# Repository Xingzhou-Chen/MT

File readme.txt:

The codes are under the path: ~/bppy/main/final/
Codes of step-wise differential sensor is in ~/bppy/main/step/
The path to the results: ~/bppy/Thesis_Results/

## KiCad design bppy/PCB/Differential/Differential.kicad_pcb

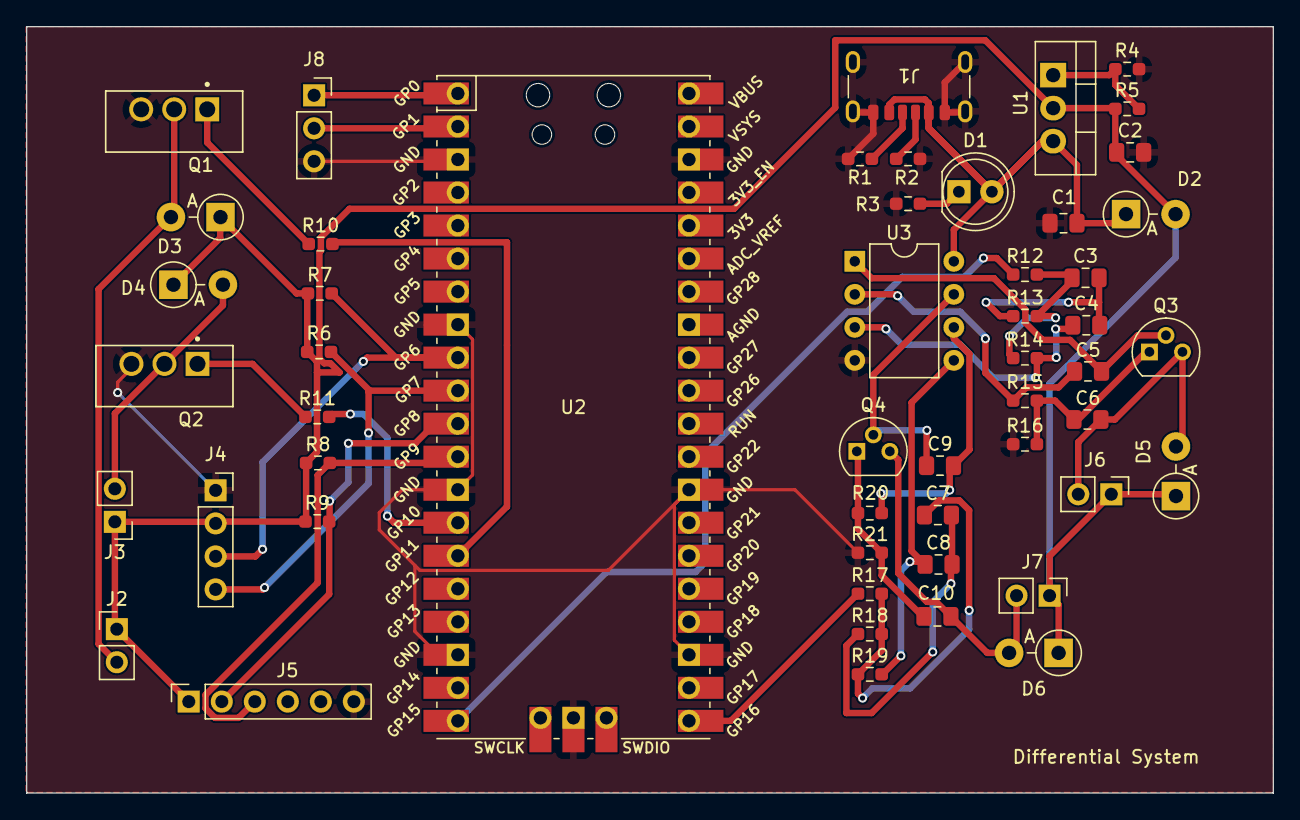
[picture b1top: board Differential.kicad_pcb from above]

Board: 2 copper layers, 95.9 x 58.9 mm, 52 parts (0 on the bottom side), 35 nets.

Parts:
C1, C6, C10: 0.1u; C_0805_2012Metric_Pad1.18x1.45mm_HandSolder
C2, C3, C7: 1u; C_0805_2012Metric_Pad1.18x1.45mm_HandSolder
C4, C5, C8, C9: 100n; C_0805_2012Metric_Pad1.18x1.45mm_HandSolder
D1: LED; LED_D5.0mm
D2, D3, D4, D5, D6: 1N4002; D_DO-41_SOD81_P3.81mm_Vertical_AnodeUp
J1: USB_C_Receptacle_PowerOnly_6P; USB_C_Receptacle_GCT_USB4125-xx-x-0190_6P_TopMnt_Horizontal
J2: Middle_Valve; PinHeader_1x02_P2.54mm_Vertical
J3: Pump; PinHeader_1x02_P2.54mm_Vertical
J4: Sensor_AMS; PinSocket_1x04_P2.54mm_Vertical
J5: Sensor_HX; PinSocket_1x06_P2.54mm_Vertical
J6: Valve_Cuff; PinHeader_1x02_P2.54mm_Vertical
J7: Valve_Baseline; PinHeader_1x02_P2.54mm_Vertical
J8: UART; PinSocket_1x03_P2.54mm_Vertical
Q1, Q2: IRLIZ44N; TO254P1054X469X1930-3
Q3, Q4: 2N2222A; TO-92
R1, R2: 5.1k; R_0603_1608Metric_Pad0.98x0.95mm_HandSolder
R3: 2.52k; R_0603_1608Metric_Pad0.98x0.95mm_HandSolder
R4: 390; R_0603_1608Metric_Pad0.98x0.95mm_HandSolder
R5: 240; R_0603_1608Metric_Pad0.98x0.95mm_HandSolder
R6, R7, R8, R9: 4.7k; R_0603_1608Metric_Pad0.98x0.95mm_HandSolder
R10, R11: 1k; R_0603_1608Metric_Pad0.98x0.95mm_HandSolder
R12, R14, R15, R17, R19, R20: 100k; R_0603_1608Metric_Pad0.98x0.95mm_HandSolder
R13, R18: 33k; R_0603_1608Metric_Pad0.98x0.95mm_HandSolder
R16, R21: 10; R_0603_1608Metric_Pad0.98x0.95mm_HandSolder
U1: LM317; TO-220-3_Vertical
U2: Pico; RPi_Pico_SMD_TH
U3: NJM2114; DIP-8_W7.62mm

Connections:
+3.3V: C2.1, D2.2 (A), D3.1 (K), D4.1 (K), D5.1 (K), D6.1 (K), J2.1, J3.1, J4.2, J5.1, J6.1, J7.1, R5.1, R6.1, R7.1, R8.1, R9.1, U1.2 (VO)
+5V: C1.1, D1.2 (A), D2.1 (K), J1.A9 (VBUS), J1.B9 (VBUS), U1.3 (VI), U3.8 (V+)
/Middle_Valve: R10.2, U2.15 (GPIO11)
/Pump: R11.2, U2.14 (GPIO10)
/RX: J8.2, U2.2 (GPIO1)
/SCL0: J5.3, R8.2, U2.12 (GPIO9)
/SCL1: J4.4, R6.2, U2.10 (GPIO7)
/SDA0: J5.2, R9.2, U2.11 (GPIO8)
/SDA1: J4.3, R7.2, U2.9 (GPIO6)
/TX: J8.1, U2.1 (GPIO0)
Baseline_Valve: R17.1, U2.21 (GPIO16)
Cuff_Valve: R12.1, U2.20 (GPIO15)
GND: C1.2, C2.2, J1.A12 (GND), J1.B12 (GND), J1.S1 (SHIELD), J4.1, J5.6, J8.3, Q1.3 (S), Q2.3 (S), R1.2, R2.2, R3.1, R4.2, R16.1, R21.1, U2.3 (GND), U2.8 (GND), U2.13 (GND), U2.18 (GND), U2.23 (GND), U2.28 (GND), U2.38 (GND), U2.42 (GND), U3.4 (V-)
unnamed: C3.1, R12.2, R13.2, R14.1
unnamed: C3.2, C4.2, R13.1
unnamed: C7.1, R17.2, R18.2, R19.1
unnamed: C7.2, C8.2, R18.1
unnamed: D1.1 (K), R3.2
unnamed: D3.2 (A), J2.2, Q1.2 (D)
unnamed: D4.2 (A), J3.2, Q2.2 (D)
unnamed: C6.1, D5.2 (A), J6.2, Q3.3 (C)
unnamed: C10.1, D6.2 (A), J7.2, Q4.3 (C)
unnamed: J1.A5 (CC1), R2.1
unnamed: J1.B5 (CC2), R1.1
unnamed: Q1.1 (G), R10.1
unnamed: Q2.1 (G), R11.1
unnamed: C5.1, Q3.2 (B), U3.1
unnamed: C6.2, Q3.1 (E), R15.2, R16.2
unnamed: C9.1, Q4.2 (B), U3.7
unnamed: C10.2, Q4.1 (E), R20.2, R21.2
unnamed: R4.1, R5.2, U1.1 (ADJ)
unnamed: C4.1, R14.2, U3.3 (+)
unnamed: C5.2, R15.1, U3.2 (-)
unnamed: C8.1, R19.2, U3.5 (+)
unnamed: C9.2, R20.1, U3.6 (-)

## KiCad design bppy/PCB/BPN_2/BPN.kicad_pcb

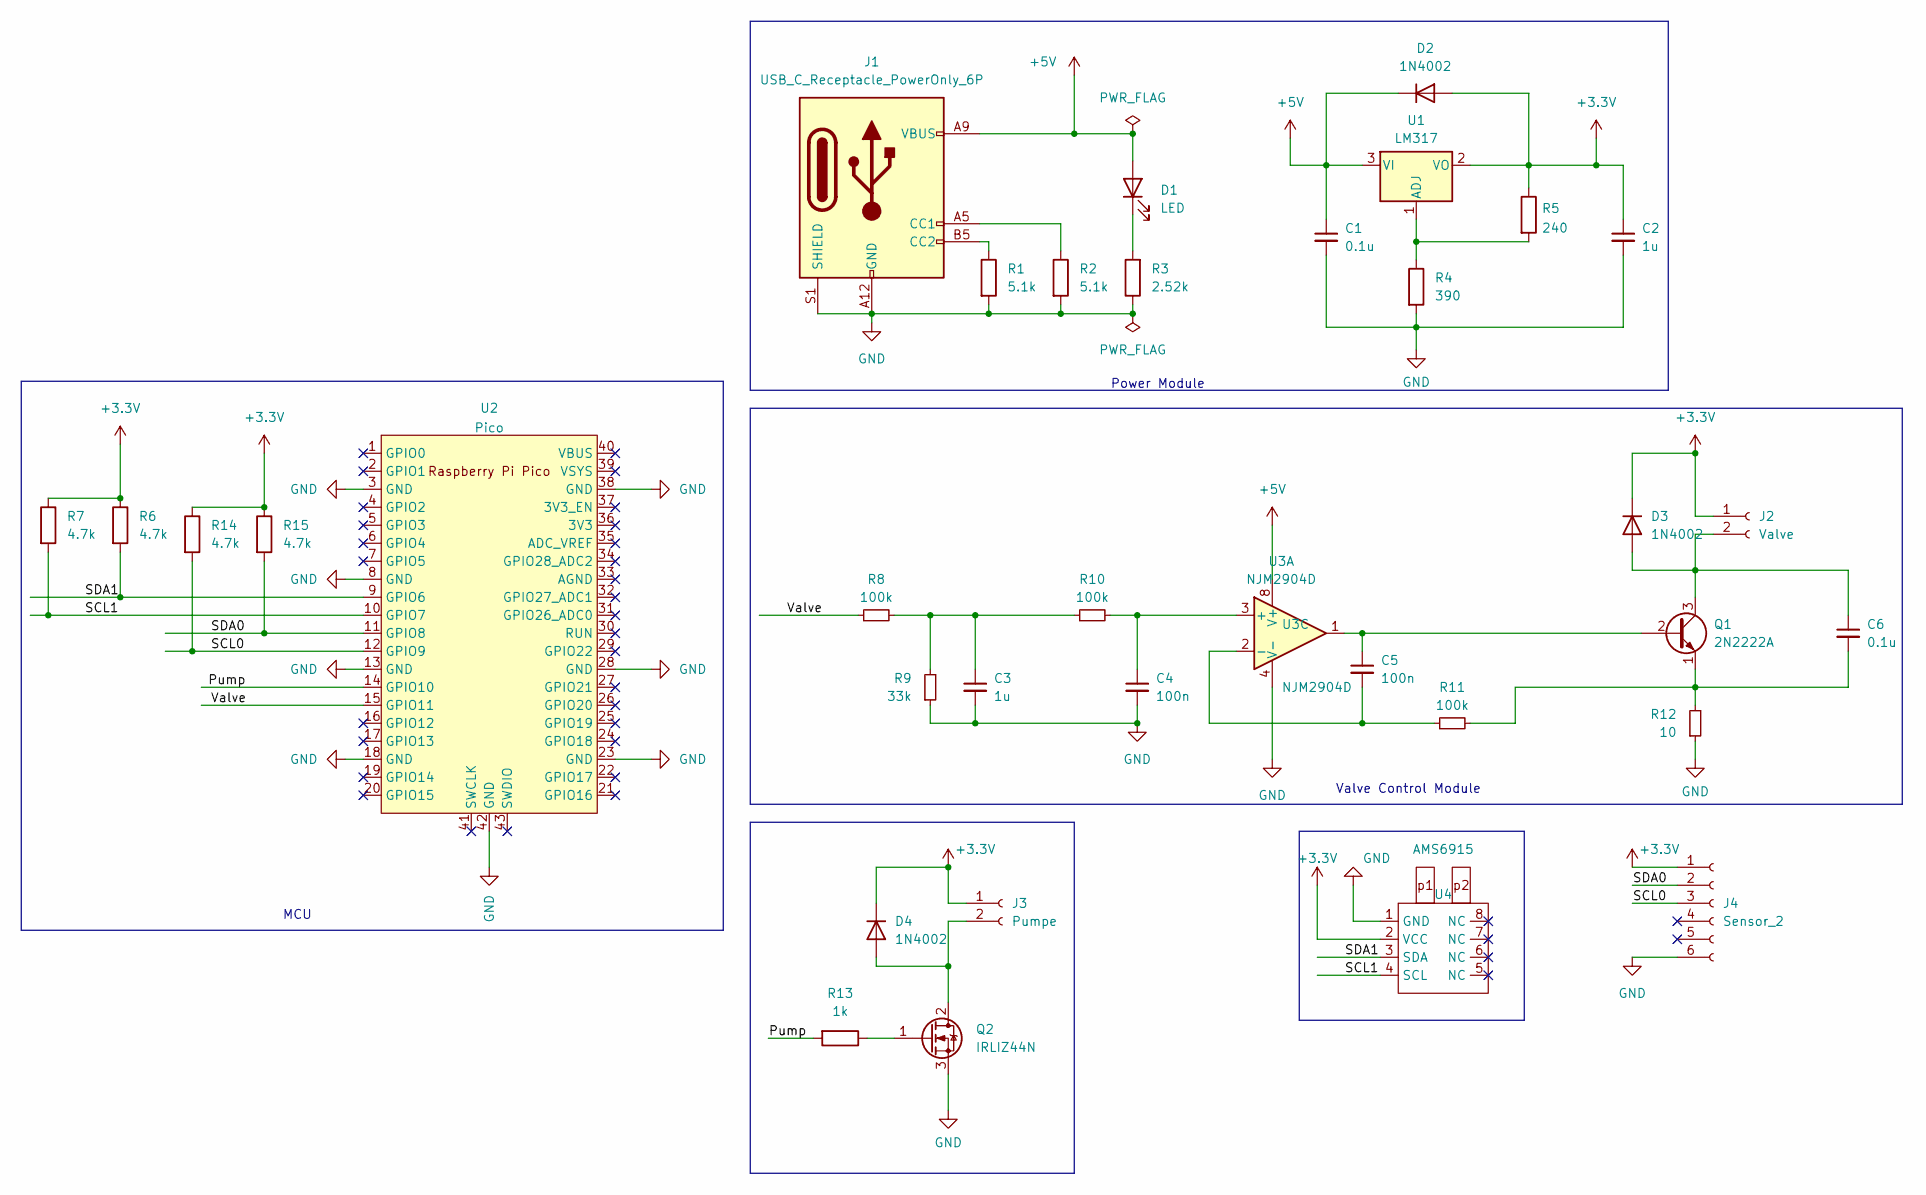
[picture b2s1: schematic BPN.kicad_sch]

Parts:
C1, C6: 0.1u; C_0805_2012Metric_Pad1.18x1.45mm_HandSolder
C2, C3: 1u; C_0805_2012Metric_Pad1.18x1.45mm_HandSolder
C4, C5: 100n; C_0805_2012Metric_Pad1.18x1.45mm_HandSolder
D1: LED; LED_D5.0mm
D2, D3, D4: 1N4002; D_DO-41_SOD81_P3.81mm_Vertical_AnodeUp
J1: USB_C_Receptacle_PowerOnly_6P; USB_C_Receptacle_GCT_USB4125-xx-x-0190_6P_TopMnt_Horizontal
J2: Valve; PinHeader_1x02_P2.54mm_Vertical
J3: Pumpe; PinHeader_1x02_P2.54mm_Vertical
J4: Sensor_2; PinSocket_1x06_P2.54mm_Vertical
Q1: 2N2222A; TO-92
Q2: IRLIZ44N; TO254P1054X469X1930-3
R1, R2: 5.1k; R_0603_1608Metric_Pad0.98x0.95mm_HandSolder
R3: 2.52k; R_0603_1608Metric_Pad0.98x0.95mm_HandSolder
R4: 390; R_0603_1608Metric_Pad0.98x0.95mm_HandSolder
R5: 240; R_0603_1608Metric_Pad0.98x0.95mm_HandSolder
R6, R7, R14, R15: 4.7k; R_0603_1608Metric_Pad0.98x0.95mm_HandSolder
R8, R10, R11: 100k; R_0603_1608Metric_Pad0.98x0.95mm_HandSolder
R9: 33k; R_0603_1608Metric_Pad0.98x0.95mm_HandSolder
R12: 10; R_0603_1608Metric_Pad0.98x0.95mm_HandSolder
R13: 1k; R_0603_1608Metric_Pad0.98x0.95mm_HandSolder
U1: LM317; TO-220-3_Vertical
U2: Pico; RPi_Pico_SMD_TH
U3: NJM2904D; DIP-8_W7.62mm_Socket
U4: AMS6915; AMS_6915_FP

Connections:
+3.3V: C2.1, D2.2 (A), D3.1 (K), D4.1 (K), J2.1, J3.1, J4.1, R5.1, R6.1, R7.1, R14.1, R15.1, U1.2 (VO), U4.2 (VCC)
+5V: C1.1, D1.2 (A), D2.1 (K), J1.A9 (VBUS), J1.B9 (VBUS), U1.3 (VI), U3.8 (V+)
/Pump: R13.2, U2.14 (GPIO10)
/SCL0: J4.3, R14.2, U2.12 (GPIO9)
/SCL1: R7.2, U2.10 (GPIO7), U4.4 (SCL)
/SDA0: J4.2, R15.2, U2.11 (GPIO8)
/SDA1: R6.2, U2.9 (GPIO6), U4.3 (SDA)
/Valve: R8.1, U2.15 (GPIO11)
unnamed: C3.1, R8.2, R9.2, R10.1
unnamed: D1.1 (K), R3.2
unnamed: C6.1, D3.2 (A), J2.2, Q1.3 (C)
unnamed: D4.2 (A), J3.2, Q2.2 (D)
unnamed: J1.A5 (CC1), R2.1
unnamed: J1.B5 (CC2), R1.1
unnamed: C5.1, Q1.2 (B), U3.1
unnamed: C6.2, Q1.1 (E), R11.2, R12.2
unnamed: Q2.1 (G), R13.1
unnamed: R4.1, R5.2, U1.1 (ADJ)
unnamed: C4.1, R10.2, U3.3 (+)
unnamed: C5.2, R11.1, U3.2 (-)

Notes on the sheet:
Power Module
MCU
Valve Control Module

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
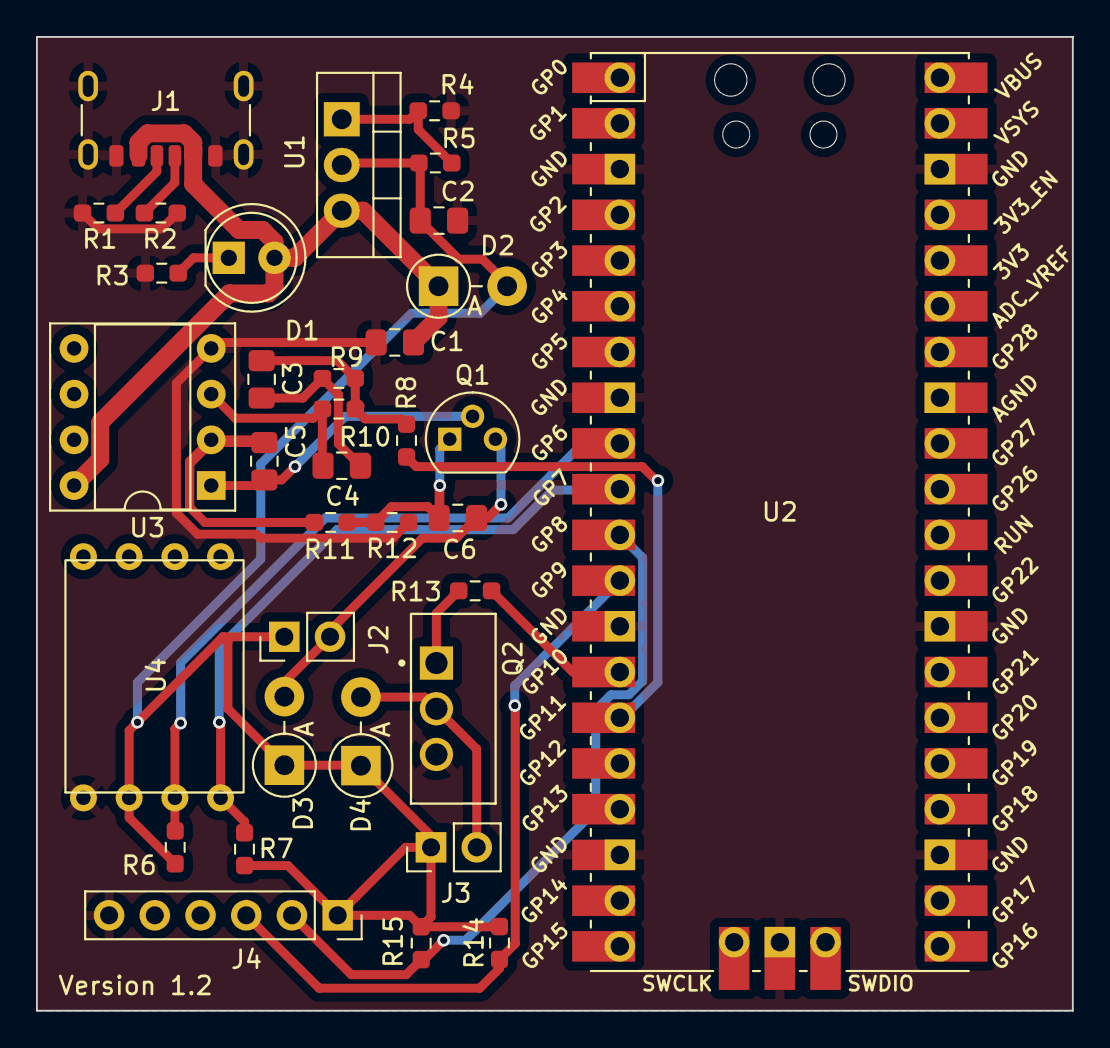
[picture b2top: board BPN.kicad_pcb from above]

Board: 2 copper layers, 57.6 x 54.1 mm, 35 parts (0 on the bottom side), 22 nets.

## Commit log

2024-01-26 pcd+filter
2024-01-27 filter_added
2024-03-20 with simulator
2024-03-20 filter Ordner
2024-03-22 could be to fast
2024-03-25 individual PID controller for both valve is required
2024-04-02 midterm
2024-04-04 much better result with faster speed
2024-04-04 add sensor class
2024-04-28 organized
2024-04-28 code organized
2024-07-09 only comment in diff_final.py
2024-07-10 modified and add comments
